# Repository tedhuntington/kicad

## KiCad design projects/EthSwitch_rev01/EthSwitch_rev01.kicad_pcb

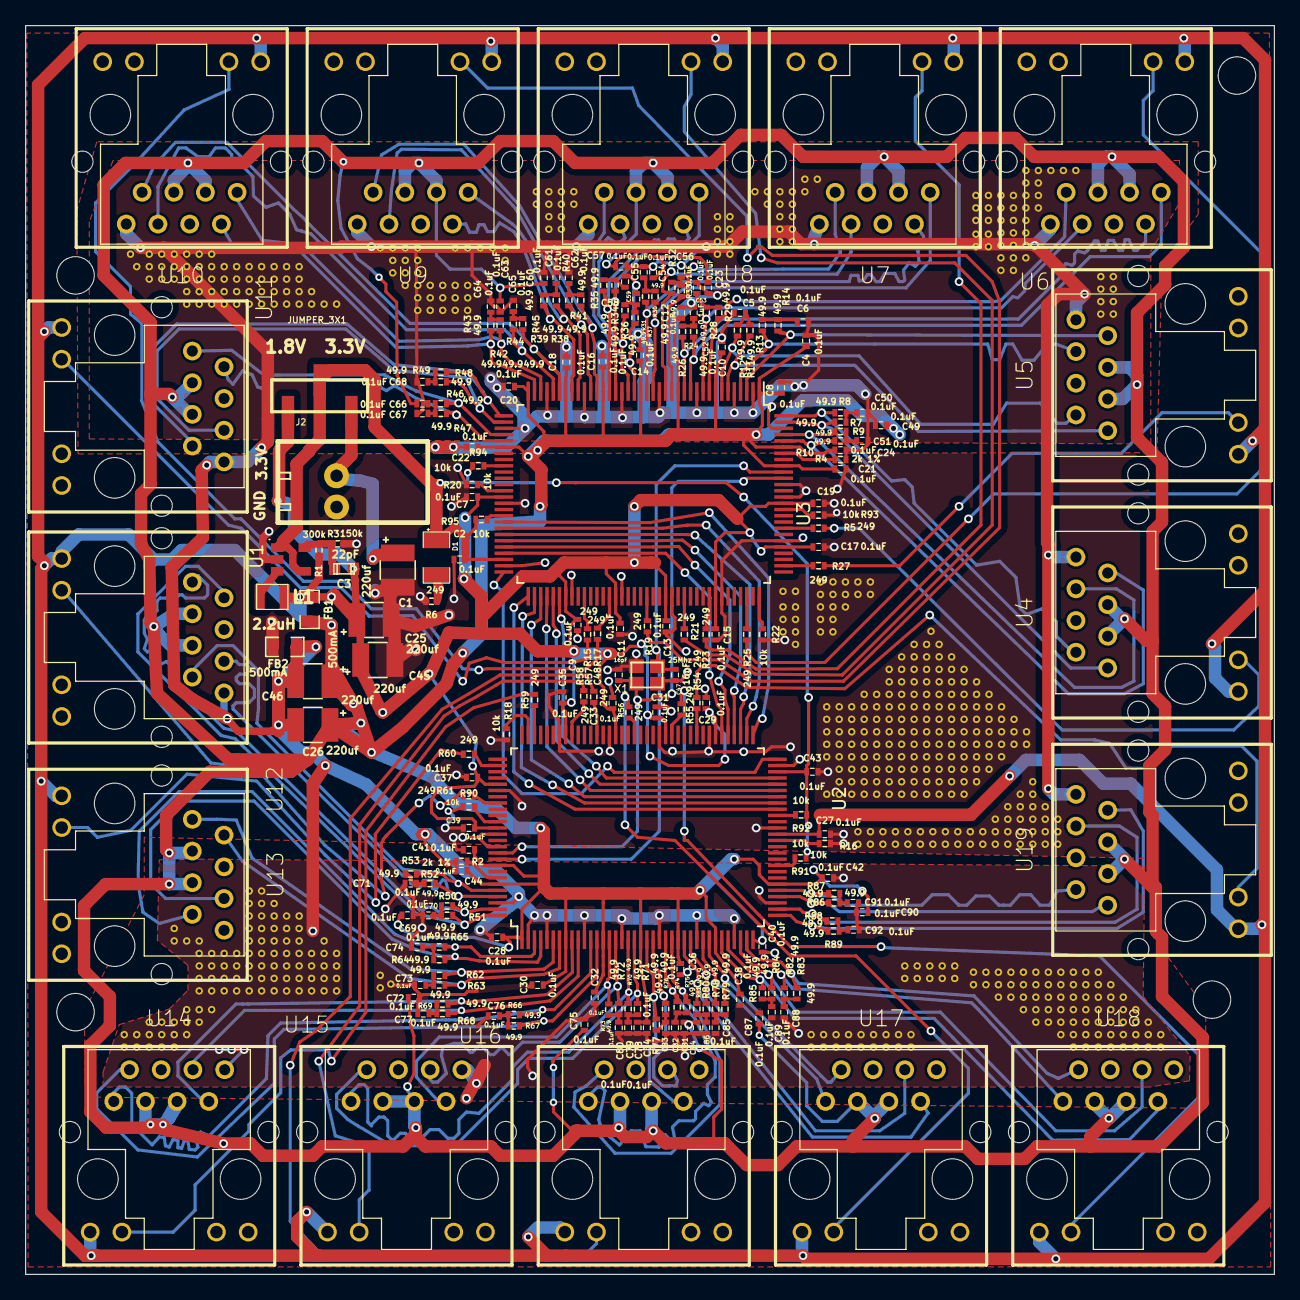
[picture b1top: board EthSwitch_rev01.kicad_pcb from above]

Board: 2 copper layers, 100.0 x 100.0 mm, 217 parts (0 on the bottom side), 164 nets.

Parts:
C1, C25, C26, C45, C46: 220uf; TED_SM3528_1311_ELEC_C
C2, C4, C5, C6, C7, C8, C9, C10, C11, C12, C13, C14, C15, C16, C17, C18, C19, C20, C21, C22, C23, C24, C27, C28, C29, C30, C31, C32, C33, C34, C35, C36, C37, C38, C39, C40, C41, C42, C43, C44, C49, C50, C51, C52, C53, C54, C55, C56, C57, C58, C59, C60, C61, C62, C63, C64, C65, C66, C67, C68, C69, C70, C71, C72, C73, C74, C75, C76, C77, C78, C79, C80, C81, C82, C83, C84, C85, C86, C87, C88, C89, C90, C91, C92: 0.1uF; TED_SM0402_C
C3: 22pF; TED_SM0603_C
C47, C48: 16pF; TED_SM0402_C
D1: LED; TED_SM1206_LED
FB1, FB2: 500mA; TED_SM0805_R
H1, H2, H3, H4: HOLE; TED_Hole_3mm
J1: Terminal_2x1; TED_TERMINAL_SPRING_2.54MM_2PIN_1989748
J2: JUMPER_3X1; TED_JUMPER_3x1_SMD
L1: 2.2uH; TED_INDUCTOR_SMD2520
R1: 300k; TED_SM0402_R
R2, R4: 2k 1%; TED_SM0402_R
R3: 150k; TED_SM0402_R
R5, R6, R15, R17, R19, R21, R23, R25, R27, R54, R55, R56, R57, R58, R59, R60, R61: 249; TED_SM0402_R
R7, R8, R9, R10, R11, R12, R13, R14, R24, R26, R28, R29, R30, R31, R32, R33, R34, R35, R36, R37, R38, R39, R40, R41, R42, R43, R44, R45, R46, R47, R48, R49, R50, R51, R52, R53, R62, R63, R64, R65, R66, R67, R68, R69, R70, R71, R72, R73, R74, R75, R76, R77, R78, R79, R80, R81, R82, R83, R84, R85, R86, R87, R88, R89: 49.9; TED_SM0402_R
R16, R18, R20, R22, R90, R91, R92, R93, R94, R95: 10k; TED_SM0402_R
U1: AP3429/A; TSOT25
U2, U3: RTL830SB_PQFP; LQFP-128_14x20mm_Pitch0.5mm
U4, U5, U6, U7, U8, U9, U10, U11, U12, U13, U14, U15, U16, U17, U18, U19: RJ45_12_PIN_UP; TED_RJ45_12pin_Up
X1: 25Mhz; TED_crystal_FA-20H

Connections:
+3.3V: C1.1, D1.1, J1.1, J2.1, U1.4
AGND: C4.2, C5.2, C6.2, C8.2, C10.2, C12.2, C14.2, C16.2, C18.2, C20.2, C22.2, C23.2, C24.2, C26.2, C28.2, C30.2, C32.2, C34.2, C36.2, C38.2, C40.2, C42.2, C44.2, C46.2, C49.2, C50.2, C51.2, C52.2, C53.2, C54.2, C55.2, C56.2, C57.2, C58.2, C59.2, C60.2, C61.2, C62.2, C63.2, C64.2, C65.2, C66.2, C67.2, C68.2, C69.2, C70.2, C71.2, C72.2, C73.2, C74.2, C75.2, C76.2, C77.2, C78.2, C79.2, C80.2, C81.2, C82.2, C83.2, C84.2, C85.2, C86.2, C87.2, C88.2, C89.2, C90.2, C91.2, C92.2, FB2.2, R2.2, R4.2, U2.2, U2.5, U2.11, U2.17, U2.23, U2.29, U2.35, U2.41, U2.126, U3.2, U3.5, U3.11, U3.17, U3.23, U3.29, U3.35, U3.41, U3.126, U4.8, U5.8, U6.8, U7.8, U8.8, U9.8, U10.8, U11.8, U12.8, U13.8, U14.8, U15.8, U16.8, U17.8, U18.8, U19.8
GND: C1.2, C2.2, C7.2, C9.2, C11.2, C13.2, C15.2, C17.2, C19.2, C21.2, C25.2, C27.2, C29.2, C31.2, C33.2, C35.2, C37.2, C39.2, C41.2, C43.2, C45.2, C47.1, C48.2, FB2.1, J1.2, R3.2, R6.2, R16.2, R18.2, R20.2, R22.2, R90.1, R93.1, U1.2, U2.53, U2.63, U2.72, U2.80, U2.88, U2.96, U2.108, U2.115, U2.117, U3.53, U3.63, U3.72, U3.80, U3.88, U3.96, U3.108, U3.115, U3.117, X1.2, X1.4
GreenLED0: R5.2, U4.10
GreenLED1: R27.2, U5.10
GreenLED2: R25.2, U6.10
GreenLED3: R23.2, U7.10
GreenLED4: R21.2, U8.10
GreenLED5: R19.2, U9.10
GreenLED6: R17.2, U10.10
GreenLED7: R15.2, U11.10
GreenLED8: R61.2, U12.10
GreenLED9: R60.2, U13.10
GreenLED10: R59.2, U14.10
GreenLED11: R58.2, U15.10
GreenLED12: R57.2, U16.10
GreenLED13: R56.2, U17.10
GreenLED14: R55.2, U18.10
GreenLED15: R54.2, U19.10
MCOL: U2.64, U3.64
MRXC: U2.56, U3.65
MRXDV: U2.57, U3.66
MRXD[0]: U2.58, U3.67
MRXD[1]: U2.59, U3.68
MRXD[2]: U2.60, U3.69
MRXD[3]: U2.61, U3.70
MTXC: U2.65, U3.56
MTXD[0]: U2.67, U3.58
MTXD[1]: U2.68, U3.59
MTXD[2]: U2.69, U3.60
MTXD[3]: U2.70, U3.61
MTXEN: U2.66, U3.57
unnamed: C3.2, R1.2, R3.1, U1.5
unnamed: C5.1, R11.2, R12.1
unnamed: C6.1, R13.2, R14.1
unnamed: C50.1, R7.2, R8.1
unnamed: C51.1, R9.2, R10.1
unnamed: C52.1, R24.2, R26.1
unnamed: C53.1, R28.2, R29.1
unnamed: C55.1, R30.2, R31.1
unnamed: C56.1, R32.2, R33.1
unnamed: C58.1, R34.2, R35.1
unnamed: C59.1, R36.2, R37.1
unnamed: C61.1, R38.2, R39.1
unnamed: C62.1, R40.2, R41.1
unnamed: C64.1, R42.2, R43.1
unnamed: C65.1, R44.2, R45.1
unnamed: C67.1, R46.2, R47.1
unnamed: C68.1, R48.2, R49.1
unnamed: C70.1, R50.2, R51.1
unnamed: C71.1, R52.2, R53.1
unnamed: C73.1, R62.2, R63.1
unnamed: C74.1, R64.2, R65.1
unnamed: C76.1, R66.2, R67.1
unnamed: C77.1, R68.2, R69.1
unnamed: C79.1, R70.2, R71.1
unnamed: C80.1, R72.2, R73.1
unnamed: C82.1, R74.2, R75.1
unnamed: C83.1, R76.2, R77.1
unnamed: C85.1, R78.2, R79.1
unnamed: C86.1, R80.2, R81.1
unnamed: C88.1, R82.2, R83.1
unnamed: C89.1, R84.2, R85.1
unnamed: C91.1, R86.2, R87.1
unnamed: C92.1, R88.2, R89.1
unnamed: D1.2, R6.1
unnamed: L1.1, U1.3
unnamed: R2.1, U2.122
unnamed: R4.1, U3.122
unnamed: R5.1, U3.110
unnamed: R15.1, U3.74
unnamed: R16.1, U2.51
unnamed: R17.1, U3.78
unnamed: R18.1, U2.101
unnamed: R19.1, U3.84
unnamed: R20.1, U3.51
unnamed: R21.1, U3.90
unnamed: R22.1, U3.102
unnamed: R23.1, U3.94
unnamed: R25.1, U3.100
unnamed: R27.1, U3.104
unnamed: R54.1, U2.74
unnamed: R55.1, U2.78
unnamed: R56.1, U2.84
unnamed: R57.1, U2.90
unnamed: R58.1, U2.94
unnamed: R59.1, U2.100
unnamed: R60.1, U2.104
unnamed: R61.1, U2.110
unnamed: R90.2, U2.113
unnamed: R91.2, U2.47
unnamed: R92.2, U2.55
unnamed: R93.2, U3.113
unnamed: R94.2, U3.47
unnamed: R95.2, U3.55
RXN0: R10.2, U3.124, U4.7
RXN1: R14.2, U3.3, U5.7
RXN2: R29.2, U3.9, U6.7
RXN3: R33.2, U3.15, U7.7
RXN4: R37.2, U3.21, U8.7
RXN5: R41.2, U3.27, U9.7
RXN6: R45.2, U3.33, U10.7
RXN7: R49.2, U3.39, U11.7
RXN8: R53.2, U2.124, U12.7
RXN9: R65.2, U2.3, U13.7
RXN10: R69.2, U2.9, U14.7
RXN11: R73.2, U2.15, U15.7
RXN12: R77.2, U2.21, U16.7
RXN13: R81.2, U2.27, U17.7
RXN14: R85.2, U2.33, U18.7
RXN15: R89.2, U2.39, U19.7
RXP0: R9.1, U3.125, U4.6
RXP1: R13.1, U3.4, U5.6
RXP2: R28.1, U3.10, U6.6
RXP3: R32.1, U3.16, U7.6
RXP4: R36.1, U3.22, U8.6
RXP5: R40.1, U3.28, U9.6
RXP6: R44.1, U3.34, U10.6
RXP7: R48.1, U3.40, U11.6
RXP8: R52.1, U2.125, U12.6
RXP9: R64.1, U2.4, U13.6
RXP10: R68.1, U2.10, U14.6
RXP11: R72.1, U2.16, U15.6
RXP12: R76.1, U2.22, U16.6
RXP13: R80.1, U2.28, U17.6
RXP14: R84.1, U2.34, U18.6
RXP15: R88.1, U2.40, U19.6
TXN0: R8.2, U3.128, U4.2
TXN1: R12.2, U3.7, U5.2
TXN2: R26.2, U3.13, U6.2
TXN3: R31.2, U3.19, U7.2
TXN4: R35.2, U3.25, U8.2
TXN5: R39.2, U3.31, U9.2
TXN6: R43.2, U3.37, U10.2
TXN7: R47.2, U3.43, U11.2
TXN8: R51.2, U2.128, U12.2
TXN9: R63.2, U2.7, U13.2
TXN10: R67.2, U2.13, U14.2
TXN11: R71.2, U2.19, U15.2
TXN12: R75.2, U2.25, U16.2
TXN13: R79.2, U2.31, U17.2
TXN14: R83.2, U2.37, U18.2
TXN15: R87.2, U2.43, U19.2
TXP0: R7.1, U3.127, U4.1
TXP1: R11.1, U3.6, U5.1
TXP2: R24.1, U3.12, U6.1
TXP3: R30.1, U3.18, U7.1
TXP4: R34.1, U3.24, U8.1
TXP5: R38.1, U3.30, U9.1
TXP6: R42.1, U3.36, U10.1
TXP7: R46.1, U3.42, U11.1
TXP8: R50.1, U2.127, U12.1
TXP9: R62.1, U2.6, U13.1
TXP10: R66.1, U2.12, U14.1
TXP11: R70.1, U2.18, U15.1
TXP12: R74.1, U2.24, U16.1
TXP13: R78.1, U2.30, U17.1
TXP14: R82.1, U2.36, U18.1
TXP15: R86.1, U2.42, U19.1
VDDA: C4.1, C8.1, C10.1, C12.1, C14.1, C16.1, C18.1, C20.1, C21.1, C22.1, C23.1, C24.1, C26.1, C28.1, C30.1, C32.1, C34.1, C36.1, C38.1, C40.1, C41.1, C42.1, C44.1, C46.1, C49.1, C54.1, C57.1, C60.1, C63.1, C66.1, C69.1, C72.1, C75.1, C78.1, C81.1, C84.1, C87.1, C90.1, FB1.2, U2.1, U2.8, U2.14, U2.20, U2.26, U2.32, U2.38, U2.44, U2.120, U2.123, U3.1, U3.8, U3.14, U3.20, U3.26, U3.32, U3.38, U3.44, U3.120, U3.123, U4.3, U4.5, U5.3, U5.5, U6.3, U6.5, U7.3, U7.5, U8.3, U8.5, U9.3, U9.5, U10.3, U10.5, U11.3, U11.5, U12.3, U12.5, U13.3, U13.5, U14.3, U14.5, U15.3, U15.5, U16.3, U16.5, U17.3, U17.5, U18.3, U18.5, U19.3, U19.5
VDDD: C3.1, C7.1, C9.1, C11.1, C13.1, C15.1, C17.1, C19.1, C25.1, C27.1, C29.1, C31.1, C33.1, C35.1, C37.1, C39.1, C45.1, FB1.1, J2.3, L1.2, R1.1, U2.52, U2.71, U2.79, U2.87, U2.95, U2.107, U2.114, U3.52, U3.71, U3.79, U3.87, U3.95, U3.107, U3.114, U4.9, U5.9, U6.9, U7.9, U8.9, U9.9, U10.9, U11.9, U12.9, U13.9, U14.9, U15.9, U16.9, U17.9, U18.9, U19.9
VDDIO: C2.1, C43.1, J2.2, R91.1, R92.1, R94.1, R95.1, U1.1, U2.62, U3.62
X1: C48.1, U2.118, U3.118, X1.1
X2: C47.2, U2.119, U3.119, X1.3

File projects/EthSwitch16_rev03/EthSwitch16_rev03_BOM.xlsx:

EthSwitch16_rev03
Sun 23 Jul 2017 09:51:01 AM PDT
Eeschema 4.0.6-e0-6349~53~ubuntu16.04.1
Component Count:194
Ref | Qnty | Value | Part | Part# | Unit Cost | Total Cost | Major Distributor | Minor Distributor
C26, C25, C1, C46, C45, | 5 | 220uf | capacitors:SM3528_1311_ELEC_C | TMCMB0J227MTRF | 0.5 | 2.5 | Mouser
C47, C48, | 2 | 16pF | capacitors:SM0603_C | GRM1885C1H160JA01D | 0.1 | 0.2 | Mouser
C8, C10, C12, C14, C16, C18, C20, C22, C24, C7, C9, C11, C13, C15, C17, C19, C2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 | 51 | 0.1uF | capacitors:SM0603_C | Vj0603V104ZXAPW1BC | 0.1 | 5.1 | Mouser
D1, | 1 | LED | led:SM1206_LED | APTR3216SGC | 0.15 | 0.15 | Mouser
FB1, FB2, | 2 | 500mA | resistors:SM0805_R | MPZ2012S601A | 0.12 | 0.24 | Mouser
H1, H2, H3, H4, | 4 | HOLE | holes:Hole_3mm |  | 0 | 0
J1, | 1 | Terminal_2x1 | connectors:TERMINAL_SPRING_2.54MM_2PIN_1989748 | 1989748 | 0.28 | 0.28 | Mouser
J2, J3, | 2 | HEADER_2X1 | connectors:HEADER_2x1 | FCI 68000-102HLF | 0.19 | 0.38 | Digi-Key
P1, P2, P3, P4, P5, P6, P7, P8, P9, P10, P11, P12, P13, | 13 | TEST_PAD | test_pads:TEST_PAD |  | 0 | 0
R18, R16, R91, R90, R92, R22, R20, R94, R93, R95, | 10 | 10k | resistors:SM0603_R | ERJ-3EKF1001V | 0.1 | 1 | Digi-Key
R2, R4, | 2 | 2k 1% | resistors:SM0603_R | RC0603FR-072KL | 0.1 | 0.2 | Digi-Key/Mouser
R53, R52, R50, R51, R65, R64, R62, R63, R69, R68, R66, R67, R73, R72, R70, R71,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 | 64 | 49.9 | resistors:SM0603_R | ERJ-3EKF49R9V | 0.1 | 6.4 | Digi-Key
R6, R61, R60, R59, R58, R57, R56, R55, R54, R5, R27, R25, R23, R21, R19, R17, R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 | 17 | 249 | resistors:SM0603_R | ERJ-2RKF2490X | 0.1 | 1.7 | Digi-Key/Mouser
U1, | 1 | AZ1084C | regulators:TO252-2 | AZ1084C | 0.65 | 0.65 | Mouser
U12, U14, U16, U18, U13, U15, U17, U19, U4, U6, U8, U10, U7, U9, U11, U5, | 16 | RJ45_12_PIN_UP | connectors:RJ45_12pin_Up_Bottom | HY951180A | 0.88 | 14.08 |  | AliExpress
U2, U3, | 2 | RTL8309SB_PQFP | ICs:LQFP-128_14x20mm_Pitch0.5mm | RTL8309SB | 1.6 | 3.2 |  | AliExpress
X1, | 1 | 25Mhz | crystals:crystal_FA-20H | FA-20H 25.0000MF20X-K3 | 0.73 | 0.73 | Mouser
 |  |  |  |  |  | 36.81

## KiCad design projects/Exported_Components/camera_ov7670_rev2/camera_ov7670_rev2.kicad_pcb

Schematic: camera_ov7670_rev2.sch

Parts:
C1, C2, C8: .1uF
C3, C4, C5: 4.7uF
C6, C7: 9pF
J1: HEADER_10X2
J2: JUMPER_3X2
R1: 10
U1: OV7670
U2: CAMERA_MOUNT_AND_LENS
U3: REGULATOR_1.8V
U4: PCS3P7303A
X1: CRYSTAL_W_2GND

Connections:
+1.8v: C3.1, U1.C1 (DVDD), U3.2
+2.8v: C4.1, C8.1, J1.1, R1.1, U1.F1 (DOVDD), U3.3, U4.7 (SSEXTR), U4.8 (VDD)
AVDD: C5.1, R1.2, U1.A1 (AVDD)
D0: J1.13, U1.B4 (D0)
D1: J1.8, U1.A4 (D1)
D2: J1.14, U1.B5 (D2)
D3: J1.7, U1.A5 (D3)
D4: J1.15, U1.F5 (D4)
D5: J1.6, U1.E5 (D5)
D6: J1.16, U1.F4 (D6)
D7: J1.5, U1.E4 (D7)
GND: C1.2, C2.2, C3.2, C4.2, C5.2, C6.2, C7.2, C8.2, J1.20, U1.B3 (AGND), U1.F3 (DOGND), U3.1, U4.3 (FS), U4.4 (GND), U4.6 (MR), X1.2, X1.4
HREF: J1.18, U1.D2 (HREF)
unnamed: C1.1, U1.C2 (VREF1)
unnamed: C2.1, U1.B2 (VREF2)
unnamed: C7.1, J2.4, X1.1
unnamed: C6.1, J2.3, X1.3
unnamed: J2.5, U4.2 (XOUT)
unnamed: J2.2, U4.1 (XIN_CLKIN)
PCLK: J1.4, U1.E1 (PCLK)
PWDN: J1.12, U1.B1 (PWDN)
RD0: J1.17, J2.1
RESET: J1.9, U1.F2 (RESET)
SIO_C: J1.2, U1.A3 (SIO_C)
SIO_D: J1.19, U1.A2 (SIO_D)
VSYNC: J1.3, U1.D1 (VSYNC)
XCLK: U1.E3 (XCLK), U4.5 (ModOUT)

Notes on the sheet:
TOP: EXT CLK BOTTOM: CRYSTAL

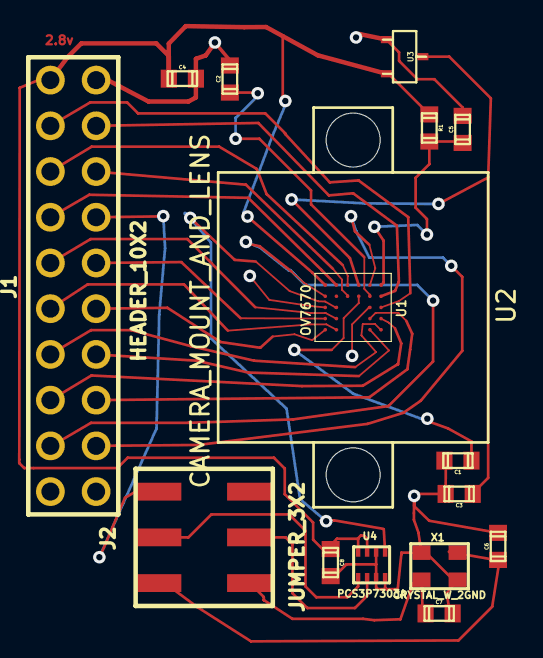
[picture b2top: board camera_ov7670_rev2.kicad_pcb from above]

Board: 2 copper layers, 16 parts (0 on the bottom side), 27 nets.

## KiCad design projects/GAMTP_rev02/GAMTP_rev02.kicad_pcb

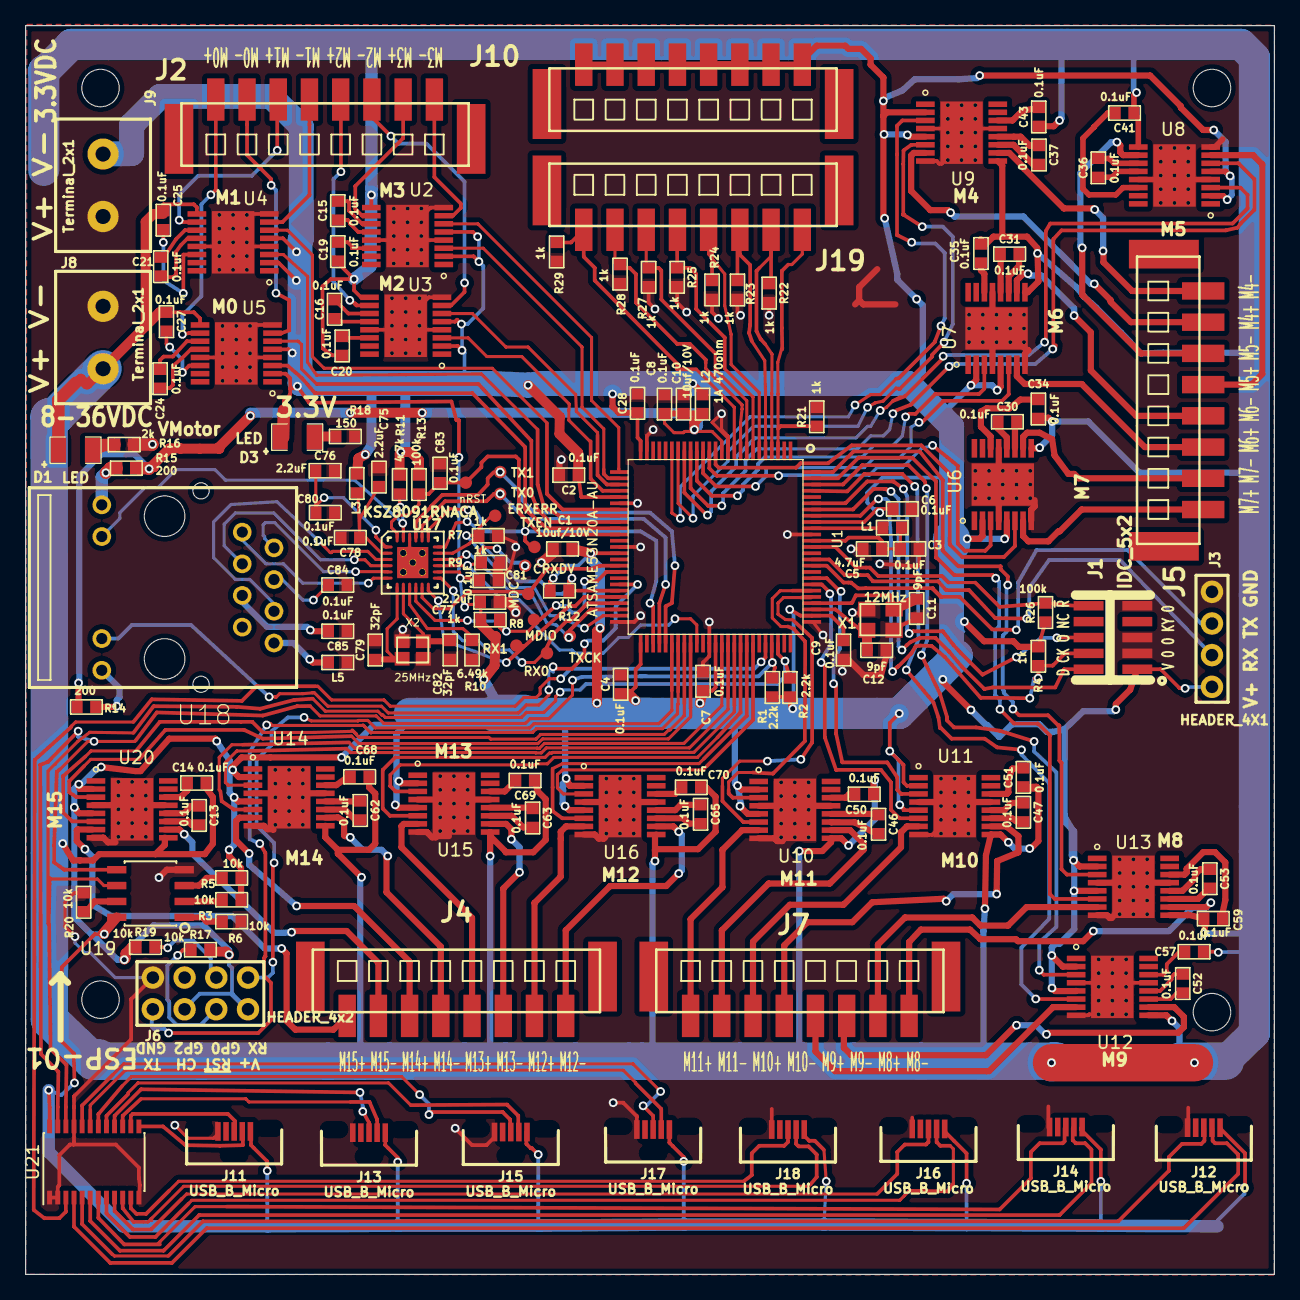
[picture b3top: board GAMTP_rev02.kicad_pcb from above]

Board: 2 copper layers, 100.0 x 100.0 mm, 148 parts (0 on the bottom side), 191 nets.

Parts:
C1, C10: 10uf/10V; TED_SM1608_0603_C
C2, C3, C4, C6, C7, C8, C9, C13, C14, C15, C16, C19, C20, C21, C24, C25, C27, C28, C30, C31, C34, C35, C36, C37, C41, C43, C46, C47, C50, C51, C52, C53, C57, C59, C62, C63, C65, C68, C69, C70, C78, C80, C81, C83, C84, C85: 0.1uF; TED_SM1608_0603_C
C5: 4.7uF; TED_SM1608_0603_C
C11, C12: 9pF; TED_SM1608_0603_C
C75, C76, C77: 2.2uF; TED_SM1608_0603_C
C79, C82: 32pF; TED_SM1608_0603_C
D1, D3: LED; TED_SM1206_LED
H1, H2, H3, H4: HOLE; TED_Hole_3mm
J1: IDC_5x2; TED_IDC_5x2_1.27pitch_SMD_nm
J2, J4, J5, J7: Terminal_8x1_rev; TED_Terminal_8x1_1814760
J3: HEADER_4X1; TED_HEADER_4x1
J6: HEADER_4x2; TED_HEADER_4x2
J8, J9: Terminal_2x1; TED_TERMINAL_5mm_2x1
J10, J19: TERMINAL_8X1; TED_Terminal_8x1_1814760
J11, J12, J13, J14, J15, J16, J17, J18: USB_B_Micro; TED_USB_MICRO_SMT
L1, L2, L3, L5: 1A 470ohm; TED_SM0603_R
P1: MDC; TED_TEST_PAD
P2: MDIO; TED_TEST_PAD
P3: nRST; TED_TEST_PAD
P4: TXCK; TED_TEST_PAD
P5: ERXERR; TED_TEST_PAD
P6: RX0; TED_TEST_PAD
P7: RX1; TED_TEST_PAD
P8: TXEN; TED_TEST_PAD
P9: TX0; TED_TEST_PAD
P10: TX1; TED_TEST_PAD
P11: CRXDV; TED_TEST_PAD
R1, R2: 2.2k; TED_SM0603_R
R3, R5, R6, R17, R19, R20: 10k; TED_SM0603_R
R4, R7, R8, R9, R12, R21, R22, R23, R24, R25, R27, R28, R29: 1k; TED_SM0603_R
R10: 6.49k; TED_SM0603_R
R11: 4.7k; TED_SM0603_R
R13, R26: 100k; TED_SM0603_R
R14, R15: 200; TED_SM0603_R
R16: 2k; TED_SM0603_R
R18: 150; TED_SM0603_R
U1: ATSAME53N20A-AU; TED_TQFP100
U2, U3, U4, U5, U6, U7, U8, U9, U10, U11, U12, U13, U14, U15, U16, U20: DRV8800_PWP; TSSOP_16+1H
U17: KSZ8091RNACA; TED_QFN24+1
U18: RJ45_12_PIN; TED_RJ45_12pin
U19: AT24MAC402; SOIC-8
U21: TCA9548APWR; TSSOP-24_4.4x7.8mm_P0.65mm
X1: 12MHz; crystal_3.2_2.5
X2: 25MHz; TED_crystal_FA-20H

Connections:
AN0: J19.1, R21.1, U1.3
AN1: J19.2, R22.1, U1.4
AN2: J19.3, R23.1, U1.5
AN3: J19.4, R24.1, U1.6
AN4: J19.5, R25.1, U1.7
AN5: J19.6, R27.1, U1.8
AN6: J19.7, R28.1, U1.9
AN7: J19.8, R29.1, U1.10
CRXDV: P11.1, R9.1, U1.60, U17.15
ESP_RX_SAM_TX: J6.8, U1.56
ESP_TX_SAM_RX: J6.1, U1.57
GND: C1.2, C2.2, C3.2, C4.2, C5.2, C6.2, C7.2, C8.2, C9.2, C10.2, C11.2, C12.2, C28.2, C75.2, C76.2, C77.2, C78.2, C79.2, C80.2, C81.2, C82.2, C83.2, C84.2, C85.1, J1.3, J1.5, J1.9, J3.4, J6.2, J8.2, J9.2, J11.5, J12.5, J13.5, J14.5, J15.5, J16.5, J17.5, J18.5, L5.1, R3.2, R7.2, R9.2, R10.2, R16.2, R18.2, R20.1, R21.2, R22.2, R23.2, R24.2, R25.2, R27.2, R28.2, R29.2, U1.11, U1.24, U1.31, U1.38, U1.50, U1.62, U1.76, U1.90, U2.4, U2.8, U2.13, U2.17, U3.4, U3.8, U3.13, U3.17, U4.4, U4.8, U4.13, U4.17, U5.4, U5.8, U5.13, U5.17, U6.4, U6.8, U6.13, U6.17, U7.4, U7.8, U7.13, U7.17, U8.4, U8.8, U8.13, U8.17, U9.4, U9.8, U9.13, U9.17, U10.4, U10.8, U10.13, U10.17, U11.4, U11.8, U11.13, U11.17, U12.4, U12.8, U12.13, U12.17, U13.4, U13.8, U13.13, U13.17, U14.4, U14.8, U14.13, U14.17, U15.4, U15.8, U15.13, U15.17, U16.4, U16.8, U16.13, U16.17, U17.22, U17.25, U19.4, U20.4, U20.8, U20.13, U20.17, U21.1, U21.2, U21.12, U21.21, X1.2, X1.4, X2.2, X2.4
GreenLED: R11.2, U17.23, U18.10
INT15_LinkAct: R12.2, U1.45, U17.18
M0+: J2.2, U5.7
M0-: J2.1, U5.10
M0_1_PB12: U1.34, U5.6
M0_2_PB13: U1.35, U5.3
M1+: J2.4, U4.7
M1-: J2.3, U4.10
M1_1_PB10: U1.32, U4.6
M1_2_PB11: U1.33, U4.3
M2+: J2.6, U3.7
M2-: J2.5, U3.10
M2_1_PA10: U1.28, U3.6
M2_2_PA11: U1.29, U3.3
M3+: J2.8, U2.7
M3-: J2.7, U2.10
M3_1_PA08: U1.26, U2.6
M3_2_PA09: U1.27, U2.3
M4+: J5.2, U9.7
M4-: J5.1, U9.10
M4_1_PA06: U1.19, U9.6
M4_2_PA07: U1.20, U9.3
M5+: J5.4, U8.7
M5-: J5.3, U8.10
M5_1_PA04: U1.17, U8.6
M5_2_PA05: U1.18, U8.3
M6+: J5.6, U7.7
M6-: J5.5, U7.10
M6_1_PB08: U1.15, U7.6
M6_2_PB09: U1.16, U7.3
M7+: J5.8, U6.7
M7-: J5.7, U6.10
M7_1_PB06: U1.13, U6.6
M7_2_PB07: U1.14, U6.3
M8+: J7.2, U13.7
M8-: J7.1, U13.10
M8_1_PB02: U1.99, U13.6
M8_2_PB03: U1.100, U13.3
M9+: J7.4, U12.7
M9-: J7.3, U12.10
M9_1_PB00: U1.97, U12.6
M9_2_PB01: U1.98, U12.3
M10+: J7.6, U11.7
M10-: J7.5, U11.10
M10_1_PC24: U1.82, U11.6
M10_2_PC25: U1.83, U11.3
M11+: J7.8, U10.7
M11-: J7.7, U10.10
M11_1_PB24: U1.80, U10.6
M11_2_PB25: U1.81, U10.3
M12+: J4.2, U16.7
M12-: J4.1, U16.10
M12_1_PB20: U1.68, U16.6
M12_2_PB21: U1.69, U16.3
M13+: J4.4, U15.7
M13-: J4.3, U15.10
M13_1_PB18: U1.66, U15.6
M13_2_PB19: U1.67, U15.3
M14+: J4.6, U14.7
M14-: J4.5, U14.10
M14_1_PB16: U1.64, U14.6
M14_2_PB17: U1.65, U14.3
M15+: J4.8, U20.7
M15-: J4.7, U20.10
M15_1_PC18: U1.58, U20.6
M15_2_PC19: U1.59, U20.3
MDC: P1.1, U1.41, U17.11
MDIO: P2.1, R8.2, U1.42, U17.10
unnamed: C13.1, U20.12
unnamed: C13.2, U20.11
unnamed: C14.2, U20.14
unnamed: C15.1, U2.12
unnamed: C15.2, U2.11
unnamed: C16.1, U3.12
unnamed: C16.2, U3.11
unnamed: C19.2, U2.14
unnamed: C20.2, U3.14
unnamed: C21.1, U4.12
unnamed: C21.2, U4.11
unnamed: C24.1, U5.12
unnamed: C24.2, U5.11
unnamed: C25.2, U4.14
unnamed: C27.2, U5.14
unnamed: C30.1, U6.12
unnamed: C30.2, U6.11
unnamed: C31.1, U7.12
unnamed: C31.2, U7.11
unnamed: C34.2, U6.14
unnamed: C35.2, U7.14
unnamed: C36.1, U8.12
unnamed: C36.2, U8.11
unnamed: C37.1, U9.12
unnamed: C37.2, U9.11
unnamed: C41.2, U8.14
unnamed: C43.2, U9.14
unnamed: C46.1, U10.12
unnamed: C46.2, U10.11
unnamed: C47.1, U11.12
unnamed: C47.2, U11.11
unnamed: C50.2, U10.14
unnamed: C51.2, U11.14
unnamed: C52.1, U12.12
unnamed: C52.2, U12.11
unnamed: C53.1, U13.12
unnamed: C53.2, U13.11
unnamed: C57.2, U12.14
unnamed: C59.2, U13.14
unnamed: C62.1, U14.12
unnamed: C62.2, U14.11
unnamed: C63.1, U15.12
unnamed: C63.2, U15.11
unnamed: C65.1, U16.12
unnamed: C65.2, U16.11
unnamed: C68.2, U14.14
unnamed: C69.2, U15.14
unnamed: C70.2, U16.14
unnamed: C75.1, C78.1, L3.2, U17.2
unnamed: C76.1, C80.1, U17.1
unnamed: C79.1, U17.7, X2.1
unnamed: C82.1, U17.8, X2.3
unnamed: C84.1, U18.4
unnamed: C85.2, U18.5
unnamed: D1.2, R16.1
unnamed: D3.2, R18.1
unnamed: J6.5, R17.1
unnamed: J6.6, R19.2
unnamed: R3.1, U19.1
unnamed: R5.1, U19.3
unnamed: R6.1, U19.2
unnamed: R10.1, U17.9
unnamed: R14.1, U18.12
unnamed: R15.1, U18.9
unnamed: R20.2, U19.7
RJ45_GND: L5.2, U18.8
RX0: P6.1, U1.47, U17.13
RX1: P7.1, U1.46, U17.12
RXER: P5.1, R7.1, U1.49, U17.17
RX_N: U17.3, U18.6
RX_P: U17.4, U18.3
SC0: J12.3, U21.5
SC1: J14.3, U21.7
SC2: J16.3, U21.9
SC3: J18.3, U21.11
SC4: J11.3, U21.14
SC5: J13.3, U21.16
SC6: J15.3, U21.18
SC7: J17.3, U21.20
SCL_MAC: R2.1, U1.73, U19.6, U21.22
SD0: J12.2, U21.4
SD1: J14.2, U21.6
SD2: J16.2, U21.8
SD3: J18.2, U21.10
SD4: J11.2, U21.13
SD5: J13.2, U21.15
SD6: J15.2, U21.17
SD7: J17.2, U21.19
SDA_MAC: R1.1, U1.72, U19.5, U21.23
SWCLK: J1.4, R4.2, U1.93
SWDIO: J1.2, U1.94
SWO: J1.6, U1.95
TX0: P9.1, U1.54, U17.20
TX1: P10.1, U1.55, U17.21
TXCK: P4.1, U1.48, U17.16
TXEN: P8.1, U1.53, U17.19
TX_N: U17.5, U18.2
TX_P: U17.6, U18.1
USART0RX: J3.2, U1.86
USART0TX: J3.3, U1.85
VDDANA: C8.1, C10.1, L2.2, R14.2, R15.2, U1.12
VDDIO: C1.1, C2.1, C4.1, C6.1, C7.1, C9.1, C28.1, C77.1, C81.1, D3.1, J1.1, J3.1, J6.3, J6.7, J9.1, J10.1, J10.2, J10.3, J10.4, J10.5, J10.6, J10.7, J10.8, J11.1, J12.1, J13.1, J14.1, J15.1, J16.1, J17.1, J18.1, L2.1, L3.1, R1.2, R2.2, R4.1, R5.2, R6.2, R8.1, R11.1, R12.1, R13.1, R17.2, R19.1, R26.1, U1.25, U1.30, U1.39, U1.51, U1.63, U1.77, U1.92, U2.2, U2.5, U3.2, U3.5, U4.2, U4.5, U5.2, U5.5, U6.2, U6.5, U7.2, U7.5, U8.2, U8.5, U9.2, U9.5, U10.2, U10.5, U11.2, U11.5, U12.2, U12.5, U13.2, U13.5, U14.2, U14.5, U15.2, U15.5, U16.2, U16.5, U17.14, U19.8, U20.2, U20.5, U21.24
VDD_MCU_VDDCORE: C3.1, C5.1, L1.2, U1.89
VDD_MCU_VSW: L1.1, U1.91
VMotor: C14.1, C19.1, C20.1, C25.1, C27.1, C34.1, C35.1, C41.1, C43.1, C50.1, C51.1, C57.1, C59.1, C68.1, C69.1, C70.1, D1.1, J8.1, U2.9, U3.9, U4.9, U5.9, U6.9, U7.9, U8.9, U9.9, U10.9, U11.9, U12.9, U13.9, U14.9, U15.9, U16.9, U20.9
XIN: C12.1, U1.78, X1.3
XOUT: C11.1, U1.79, X1.1
YellowLED: U1.44, U18.11
~I2C_Reset~: U1.71, U21.3
~RESET~: J1.10, R26.2, U1.88
~RST#~: C83.1, P3.1, R13.2, U1.36, U17.24

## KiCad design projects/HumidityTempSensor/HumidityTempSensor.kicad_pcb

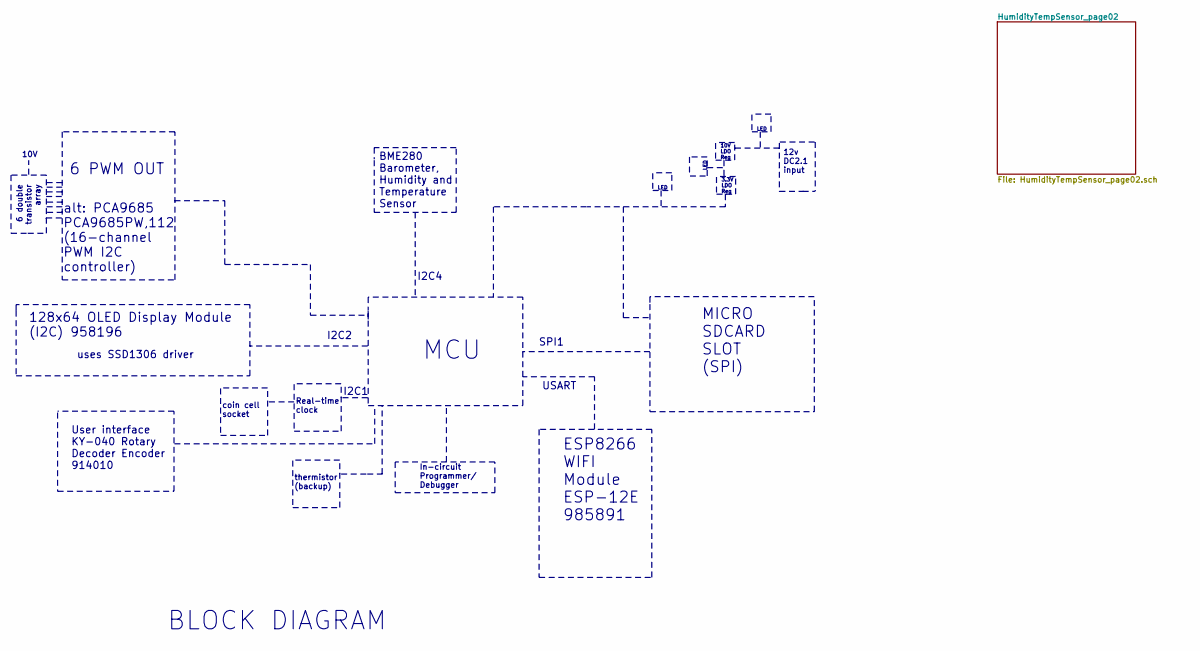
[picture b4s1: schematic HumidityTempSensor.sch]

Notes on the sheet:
MCU
BME280 Barometer, Humidity and Temperature Sensor
MICRO SDCARD SLOT (SPI)
In-circuit Programmer/ Debugger
128x64 OLED Display Module (I2C) 958196
Real-time clock
thermistor (backup)
12v DC2.1 input
User interface KY-040 Rotary Decoder Encoder 914010
ESP8266 WIFI Module ESP-12E 985891
BLOCK DIAGRAM
uses SSD1306 driver
6 PWM OUT
I2C1
I2C2
SPI1
I2C4
USART
alt: PCA9685 PCA9685PW,112 (16-channel PWM I2C controller)
6 double transistor array
coin cell socket
10V LDO Reg
3.3V LDO Reg
LED
10V
